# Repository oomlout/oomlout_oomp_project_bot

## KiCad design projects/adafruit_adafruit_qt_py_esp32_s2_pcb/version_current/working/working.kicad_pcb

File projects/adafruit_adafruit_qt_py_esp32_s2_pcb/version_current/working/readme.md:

# Adafruit-QT-Py-ESP32-S2-PCB by adafruit  
This is a harvested standardized copy of a project from github.  
The original project can be found at:  
https://github.com/adafruit/Adafruit-QT-Py-ESP32-S2-PCB  
Please consult that link for additional, details, files, and license information.  
Note: It was auto harvested and if the original repo had more than one board file or anything out of the ordinary the files here are likely not representative.

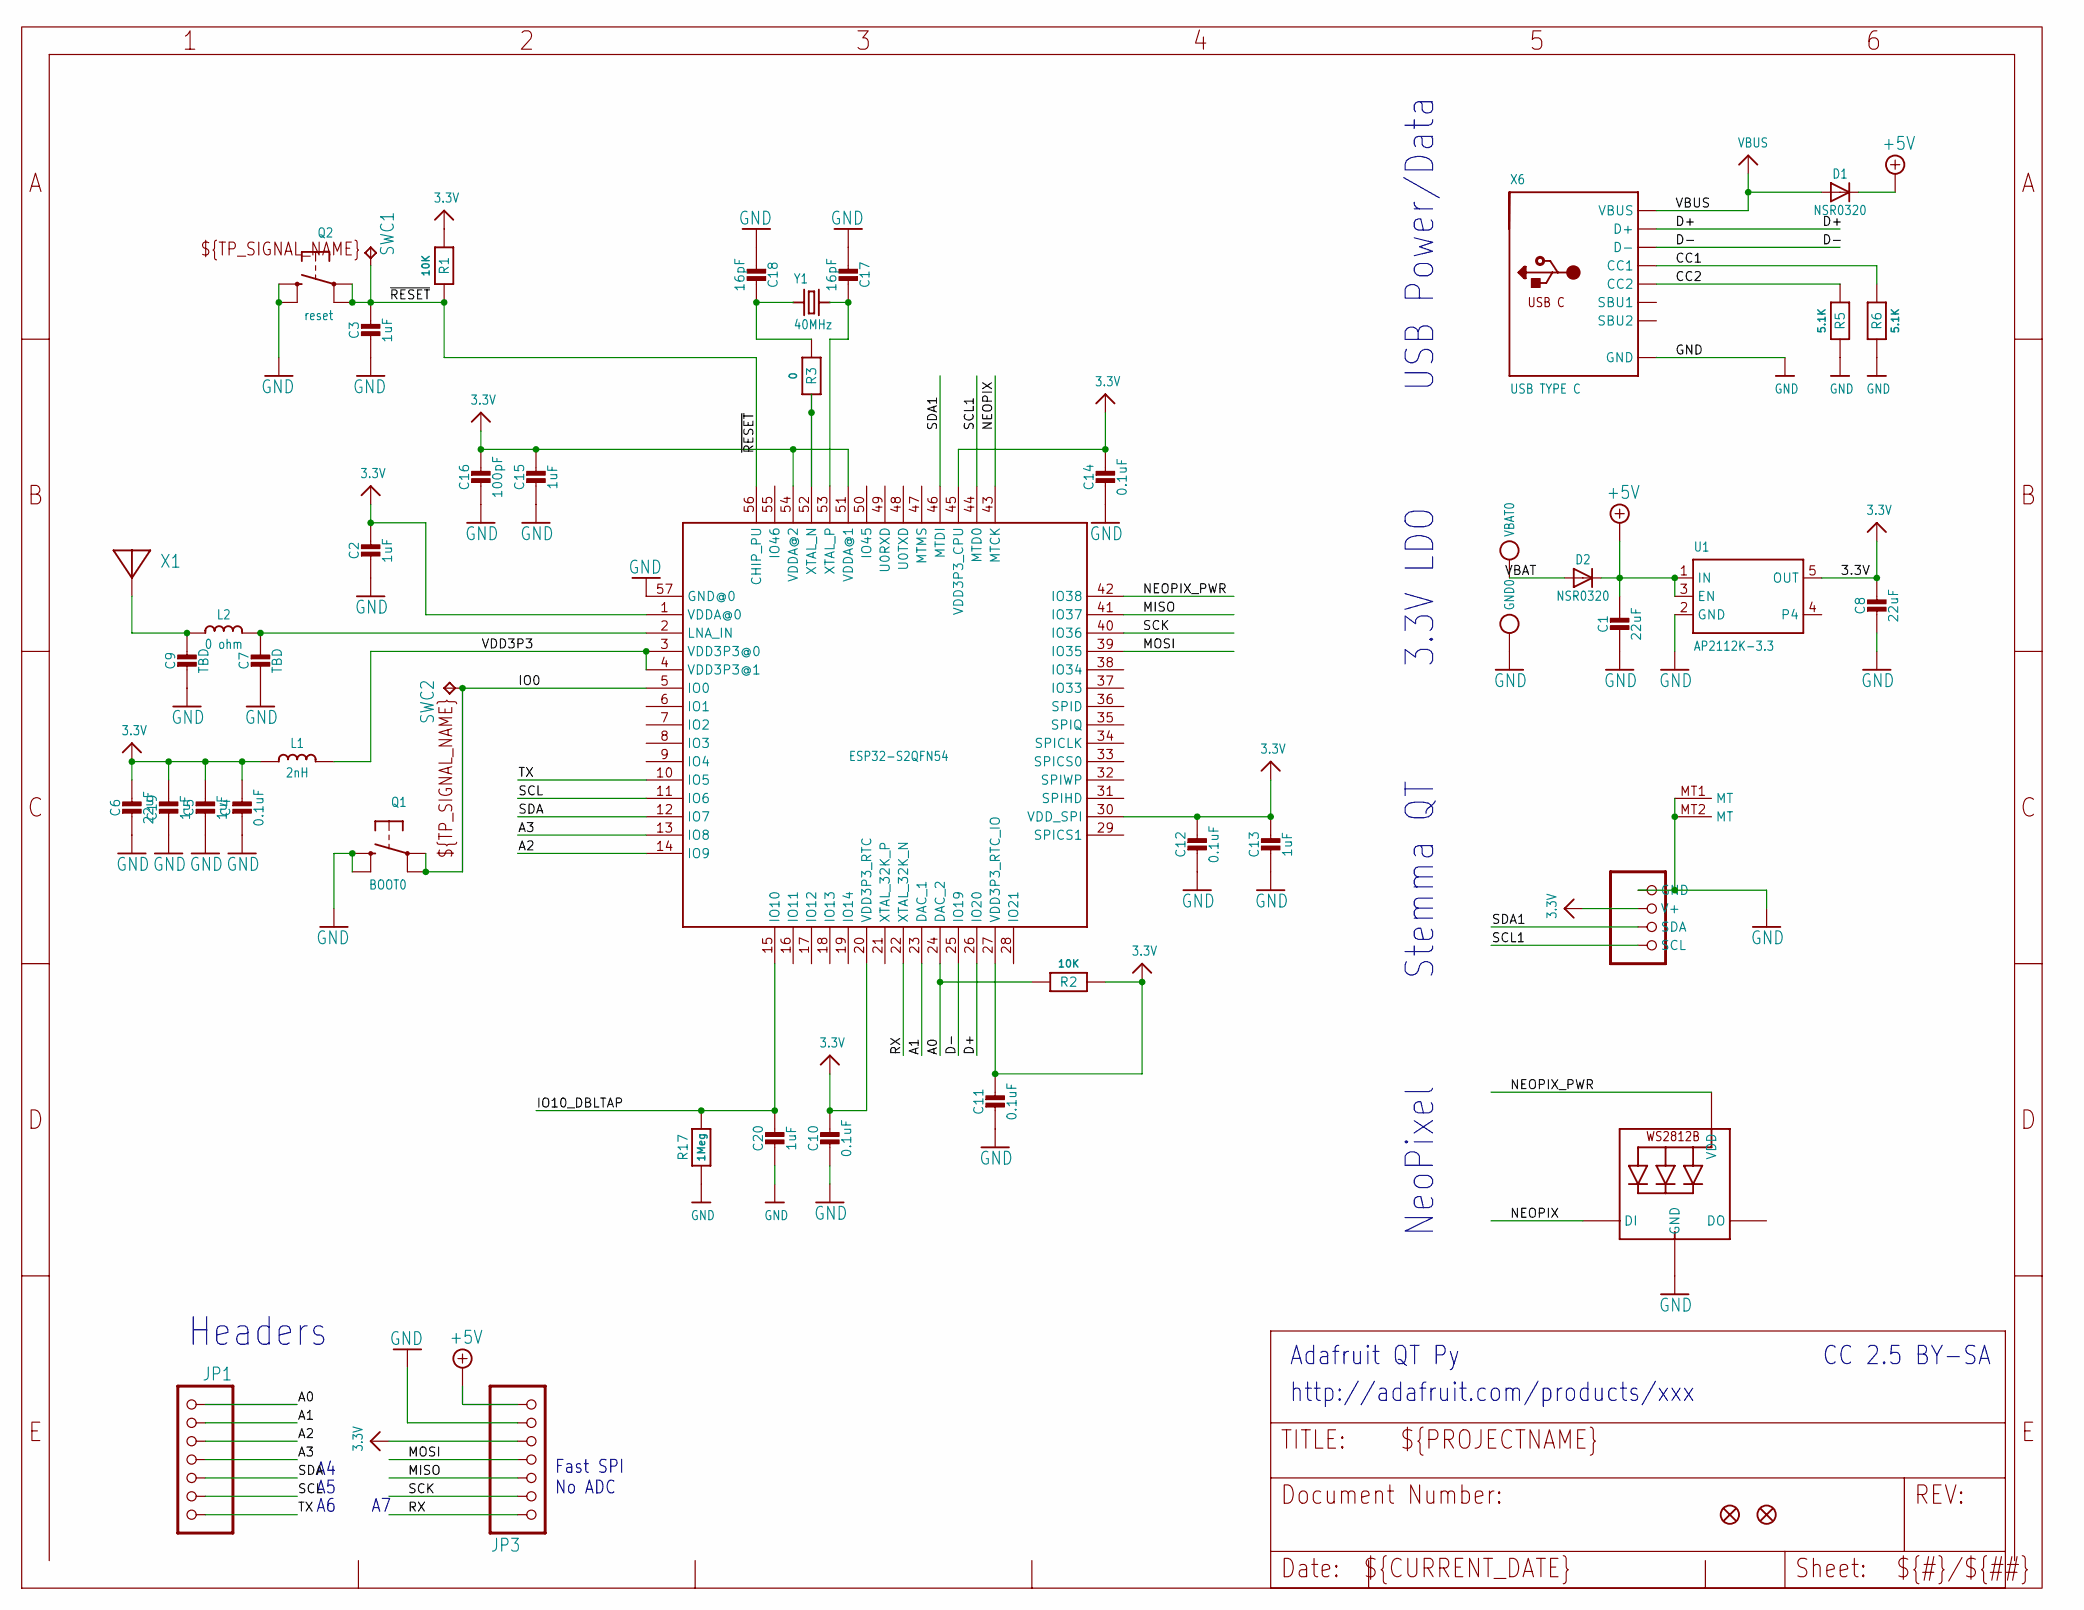
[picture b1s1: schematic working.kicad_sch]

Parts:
C1, C6, C8: 22uF; 0805-NO
C2, C3, C5, C13, C15, C19, C20: 1uF; _0402NO
C4, C10, C11, C12, C14: 0.1uF; _0402NO
C7, C9: TBD; _0402NO
C16: 100pF; _0402NO
C17, C18: 16pF; _0402NO
CONN1: STEMMA_I2C_QTSKINNY; JST_SH4_SKINNY
D1, D2: NSR0320; SOD-323_MINI
GND0: TESTPOINT_1X3; TESTPOINT_RECT_1X3MM
JP1, JP3: HEADER-1X7_CASTEL; 1X07_CASTEL
L1: 2nH; _0402
L2: 0 ohm; _0402
LED1: WS2812B_SK6805_1515; SK6805_1515
Q1: BOOT0; BTN_KMR2_4.6X2.8
Q2: reset; BTN_KMR2_4.6X2.8
R1, R2: 10K; _0402NO
R3: 0; _0402NO
R5, R6: 5.1K; _0402NO
R17: 1Meg; _0402NO
SWC1, SWC2: TPB1,27; B1,27
U1: AP2112K-3.3; SOT23-5
U$6, U$8: FIDUCIAL_1MM
U$15: ESP32-S2QFN54; QFN40P700X700X90-57T400N
VBAT0: TESTPOINT_1X3; TESTPOINT_RECT_1X3MM
X1: ANTENNA_JOHANSON_2450AT18B100; ANT_2450AT18B100
X6: USB TYPE C; USB_C_CUSB31-CFM2AX-01-X
Y1: 40MHz; CRYSTAL_2X1.6

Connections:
3.3V: C2.1, C4.1, C5.1, C6.1, C8.1, C10.1, C11.1, C12.1, C13.1, C14.1, C15.1, C16.1, C19.1, CONN1.2 (V+), JP3.5, JP3.5C (5), L1.1, R1.1, R2.1, U1.5 (OUT), U$15.1 (VDDA@0), U$15.20 (VDD3P3_RTC), U$15.27 (VDD3P3_RTC_IO), U$15.30 (VDD_SPI), U$15.45 (VDD3P3_CPU), U$15.51 (VDDA@1), U$15.54 (VDDA@2)
+5V: C1.1, D1.C, D2.C, JP3.7, JP3.7C (7), U1.1 (IN), U1.3 (EN)
A0: JP1.1, JP1.1C (1), R2.2, U$15.24 (DAC_2)
A1: JP1.2, JP1.2C (2), U$15.23 (DAC_1)
A2: JP1.3, JP1.3C (3), U$15.14 (IO9)
A3: JP1.4, JP1.4C (4), U$15.13 (IO8)
CC1: R6.2, X6.A5 (CC1)
CC2: R5.2, X6.B5 (CC2)
D+: U$15.26 (IO20), X6.A6 (D+), X6.B6 (D+)
D-: U$15.25 (IO19), X6.A7 (D-), X6.B7 (D-)
GND: C1.2, C2.2, C3.2, C4.2, C5.2, C6.2, C7.2, C8.2, C9.2, C10.2, C11.2, C12.2, C13.2, C14.2, C15.2, C16.2, C17.2, C18.2, C19.2, C20.2, CONN1.1 (GND), CONN1.MT1 (MT), CONN1.MT2 (MT), GND0.P$1, JP3.6, JP3.6C (6), LED1.4 (GND), Q1.B (S), Q1.B' (S1), Q2.B (S), Q2.B' (S1), R5.1, R6.1, R17.1, U1.2 (GND), U$15.57 (GND@0), X6.A1B12 (GND), X6.B1A12 (GND)
IO0: Q1.A, Q1.A' (P1), SWC2.TP, U$15.5 (IO0)
IO10_DBLTAP: C20.1, R17.2, U$15.15 (IO10)
MISO: JP3.3, JP3.3C (3), U$15.41 (IO37)
MOSI: JP3.4, JP3.4C (4), U$15.39 (IO35)
unnamed: C7.1, L2.2, U$15.2 (LNA_IN)
unnamed: C9.1, L2.1, X1.FP
unnamed: R3.2, U$15.52 (XTAL_N)
unnamed: C17.1, U$15.53 (XTAL_P), Y1.3 (2)
unnamed: C18.1, R3.1, Y1.1
NEOPIX: LED1.1 (DI), U$15.43 (MTCK)
NEOPIX_PWR: LED1.2 (VDD), U$15.42 (IO38)
RX: JP3.1, JP3.1C (1), U$15.22 (XTAL_32K_N)
SCK: JP3.2, JP3.2C (2), U$15.40 (IO36)
SCL: JP1.6, JP1.6C (6), U$15.11 (IO6)
SCL1: CONN1.4 (SCL), U$15.44 (MTD0)
SDA: JP1.5, JP1.5C (5), U$15.12 (IO7)
SDA1: CONN1.3 (SDA), U$15.46 (MTDI)
TX: JP1.7, JP1.7C (7), U$15.10 (IO5)
VBAT: D2.A, VBAT0.P$1
VBUS: D1.A, X6.A4B9 (VBUS), X6.B4A9 (VBUS)
VDD3P3: L1.2, U$15.3 (VDD3P3@0), U$15.4 (VDD3P3@1)
~RESET: C3.1, Q2.A, Q2.A' (P1), R1.2, SWC1.TP, U$15.56 (CHIP_PU)

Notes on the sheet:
USB Power/Data
CC 2.5 BY-SA
Adafruit QT Py
Headers
NeoPixel
http://adafruit.com/products/xxx
Fast SPI No ADC
Stemma QT
3.3V LDO

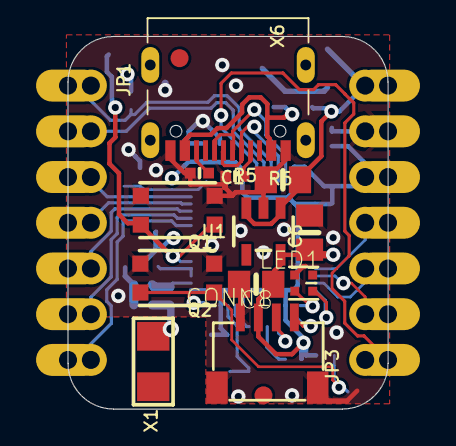
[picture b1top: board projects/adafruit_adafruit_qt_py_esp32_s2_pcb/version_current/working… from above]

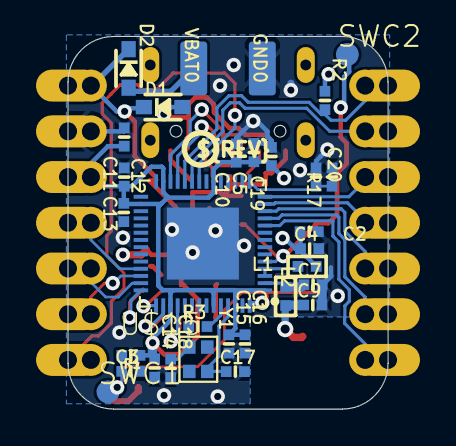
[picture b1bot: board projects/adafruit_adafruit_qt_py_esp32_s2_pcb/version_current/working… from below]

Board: 4 copper layers, 17.8 x 20.7 mm, 50 parts (33 on the bottom side), 33 nets.

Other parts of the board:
U$3: QTPYS2_TOP
U$7: QTPYS2_BOT
U$12: PCBFEAT-REV-040

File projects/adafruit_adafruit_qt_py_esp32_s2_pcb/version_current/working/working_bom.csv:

Row,Description,Part,References,Value,Footprint,Quantity Per PCB,Status,Datasheet
1,,CAP_CERAMIC_0402NO,C17 C18,16pF,_0402NO,2, ,
2,,CAP_CERAMIC_0402NO,C16,100pF,_0402NO,1, ,
3,,CAP_CERAMIC_0402NO,C4 C10 C11 C12 C14,0.1uF,_0402NO,5, ,
4,,CAP_CERAMIC_0402NO,C2 C3 C5 C13 C15 C19 C20,1uF,_0402NO,7, ,
5,,CAP_CERAMIC0805-NOOUTLINE,C1 C6 C8,22uF,0805-NO,3, ,
6,,CAP_CERAMIC_0402NO,C7 C9,TBD,_0402NO,2, ,
7,,STEMMA_I2C_QTSKINNY,CONN1,STEMMA_I2C_QTSKINNY,JST_SH4_SKINNY,1, ,
8,,DIODE_SOD323MINI,D1 D2,NSR0320,SOD-323_MINI,2, ,
9,,HEADER-1X7_CASTEL,JP1 JP3,HEADER-1X7_CASTEL,1X07_CASTEL,2, ,
10,,INDUCTOR_0402,L2,0 ohm,_0402,1, ,
11,,INDUCTOR_0402,L1,2nH,_0402,1, ,
12,,WS2812B_SK6805_1515,LED1,WS2812B_SK6805_1515,SK6805_1515,1, ,
13,,SWITCH_TACT_SMT4.6X2.8,Q1,BOOT0,BTN_KMR2_4.6X2.8,1, ,
14,,SWITCH_TACT_SMT4.6X2.8,Q2,reset,BTN_KMR2_4.6X2.8,1, ,
15,,RESISTOR_0402NO,R3,0,_0402NO,1, ,
16,,RESISTOR_0402NO,R5 R6,5.1K,_0402NO,2, ,
17,,RESISTOR_0402NO,R1 R2,10K,_0402NO,2, ,
18,,RESISTOR_0402NO,R17,1Meg,_0402NO,1, ,
19,,"TPB1,27",SWC1 SWC2,"TPB1,27","B1,27",2, ,
20,,VREG_SOT23-5,U1,AP2112K-3.3,SOT23-5,1, ,
21,,ESP32-S2QFN54,U$15,ESP32-S2QFN54,QFN40P700X700X90-57T400N,1, ,
22,,ANTENNA_JOHANSON_2450AT18B100,X1,ANTENNA_JOHANSON_2450AT18B100,ANT_2450AT18B100,1, ,
23,,USB_C,X6,USB TYPE C,USB_C_CUSB31-CFM2AX-01-X,1, ,
24,,CRYSTAL_2X1.6MM,Y1,40MHz,CRYSTAL_2X1.6,1, ,





Project info:
Schematic:,working
Variant:,default
Revision:,
Date:,2023-08-03_17-21-23
KiCad Version:,7.0.6-7.0.6~ubuntu22.04.1
Statistics:
Component Groups:,24
Component Count:,43 (0 SMD/ 0 THT)
Fitted Components:,43 (0 SMD/ 0 THT)
Number of PCBs:,1
Total Components:,43

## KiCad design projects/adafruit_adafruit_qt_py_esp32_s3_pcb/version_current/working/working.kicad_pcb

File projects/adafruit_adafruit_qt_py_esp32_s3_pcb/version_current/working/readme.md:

# OOMP Project  
## Adafruit-QT-Py-ESP32-S3-PCB  by adafruit  
  
oomp key: oomp_projects_flat_adafruit_adafruit_qt_py_esp32_s3_pcb  
(snippet of original readme)  
  
-- Adafruit QT Py ESP32-S3 WiFi Dev Board PCB  
  
<a href="http://www.adafruit.com/products/5426"><br/>  
Click here to purchase one from the Adafruit shop</a>  
  
PCB files for the Adafruit QT Py ESP32-S3 WiFi Dev Board.   
  
Format is EagleCAD schematic and board layout  
* https://www.adafruit.com/product/5426  
  
--- Description  
  
The ESP32-S3 has arrived in QT Py format - and what a great way to get started with this powerful new chip from Espressif! With dual 240 MHz cores, WiFi and BLE support, and native USB, this QT Py is great for powering your IoT projects.  
  
The ESP32-S3 is a highly-integrated, low-power, 2.4 GHz Wi-Fi System-on-Chip (SoC) solution that now has WiFi and BLE support, built-in native USB as well as some other interesting new technologies like Time of Flight distance measurements. With its state-of-the-art power and RF performance, this SoC is an ideal choice for a wide variety of application scenarios relating to the Internet of Things (IoT), wearable electronics, and smart homes.   
  
With native USB and 8 MB Flash this board will let you upgrade your existing ESP32 projects. Native USB means it can act like a keyboard or a disk drive, and no external USB-to-Serial converter required. WiFi and BLE mean it's awesome for IoT projects.  
  
OLEDs! Inertial Measurement Units! Sensors a-plenty. All plug-and-play thanks to the innovative chainable design: SparkFun Qwiic-compatible STEMMA QT connectors for the I2C bus so you don't  
  full source readme at [readme_src.md](readme_src.md)  
  
source repo at: [https://github.com/adafruit/Adafruit-QT-Py-ESP32-S3-PCB](https://github.com/adafruit/Adafruit-QT-Py-ESP32-S3-PCB)  
## Board  

## Schematic  

[schematic pdf](working_schematic.pdf)  
## Images

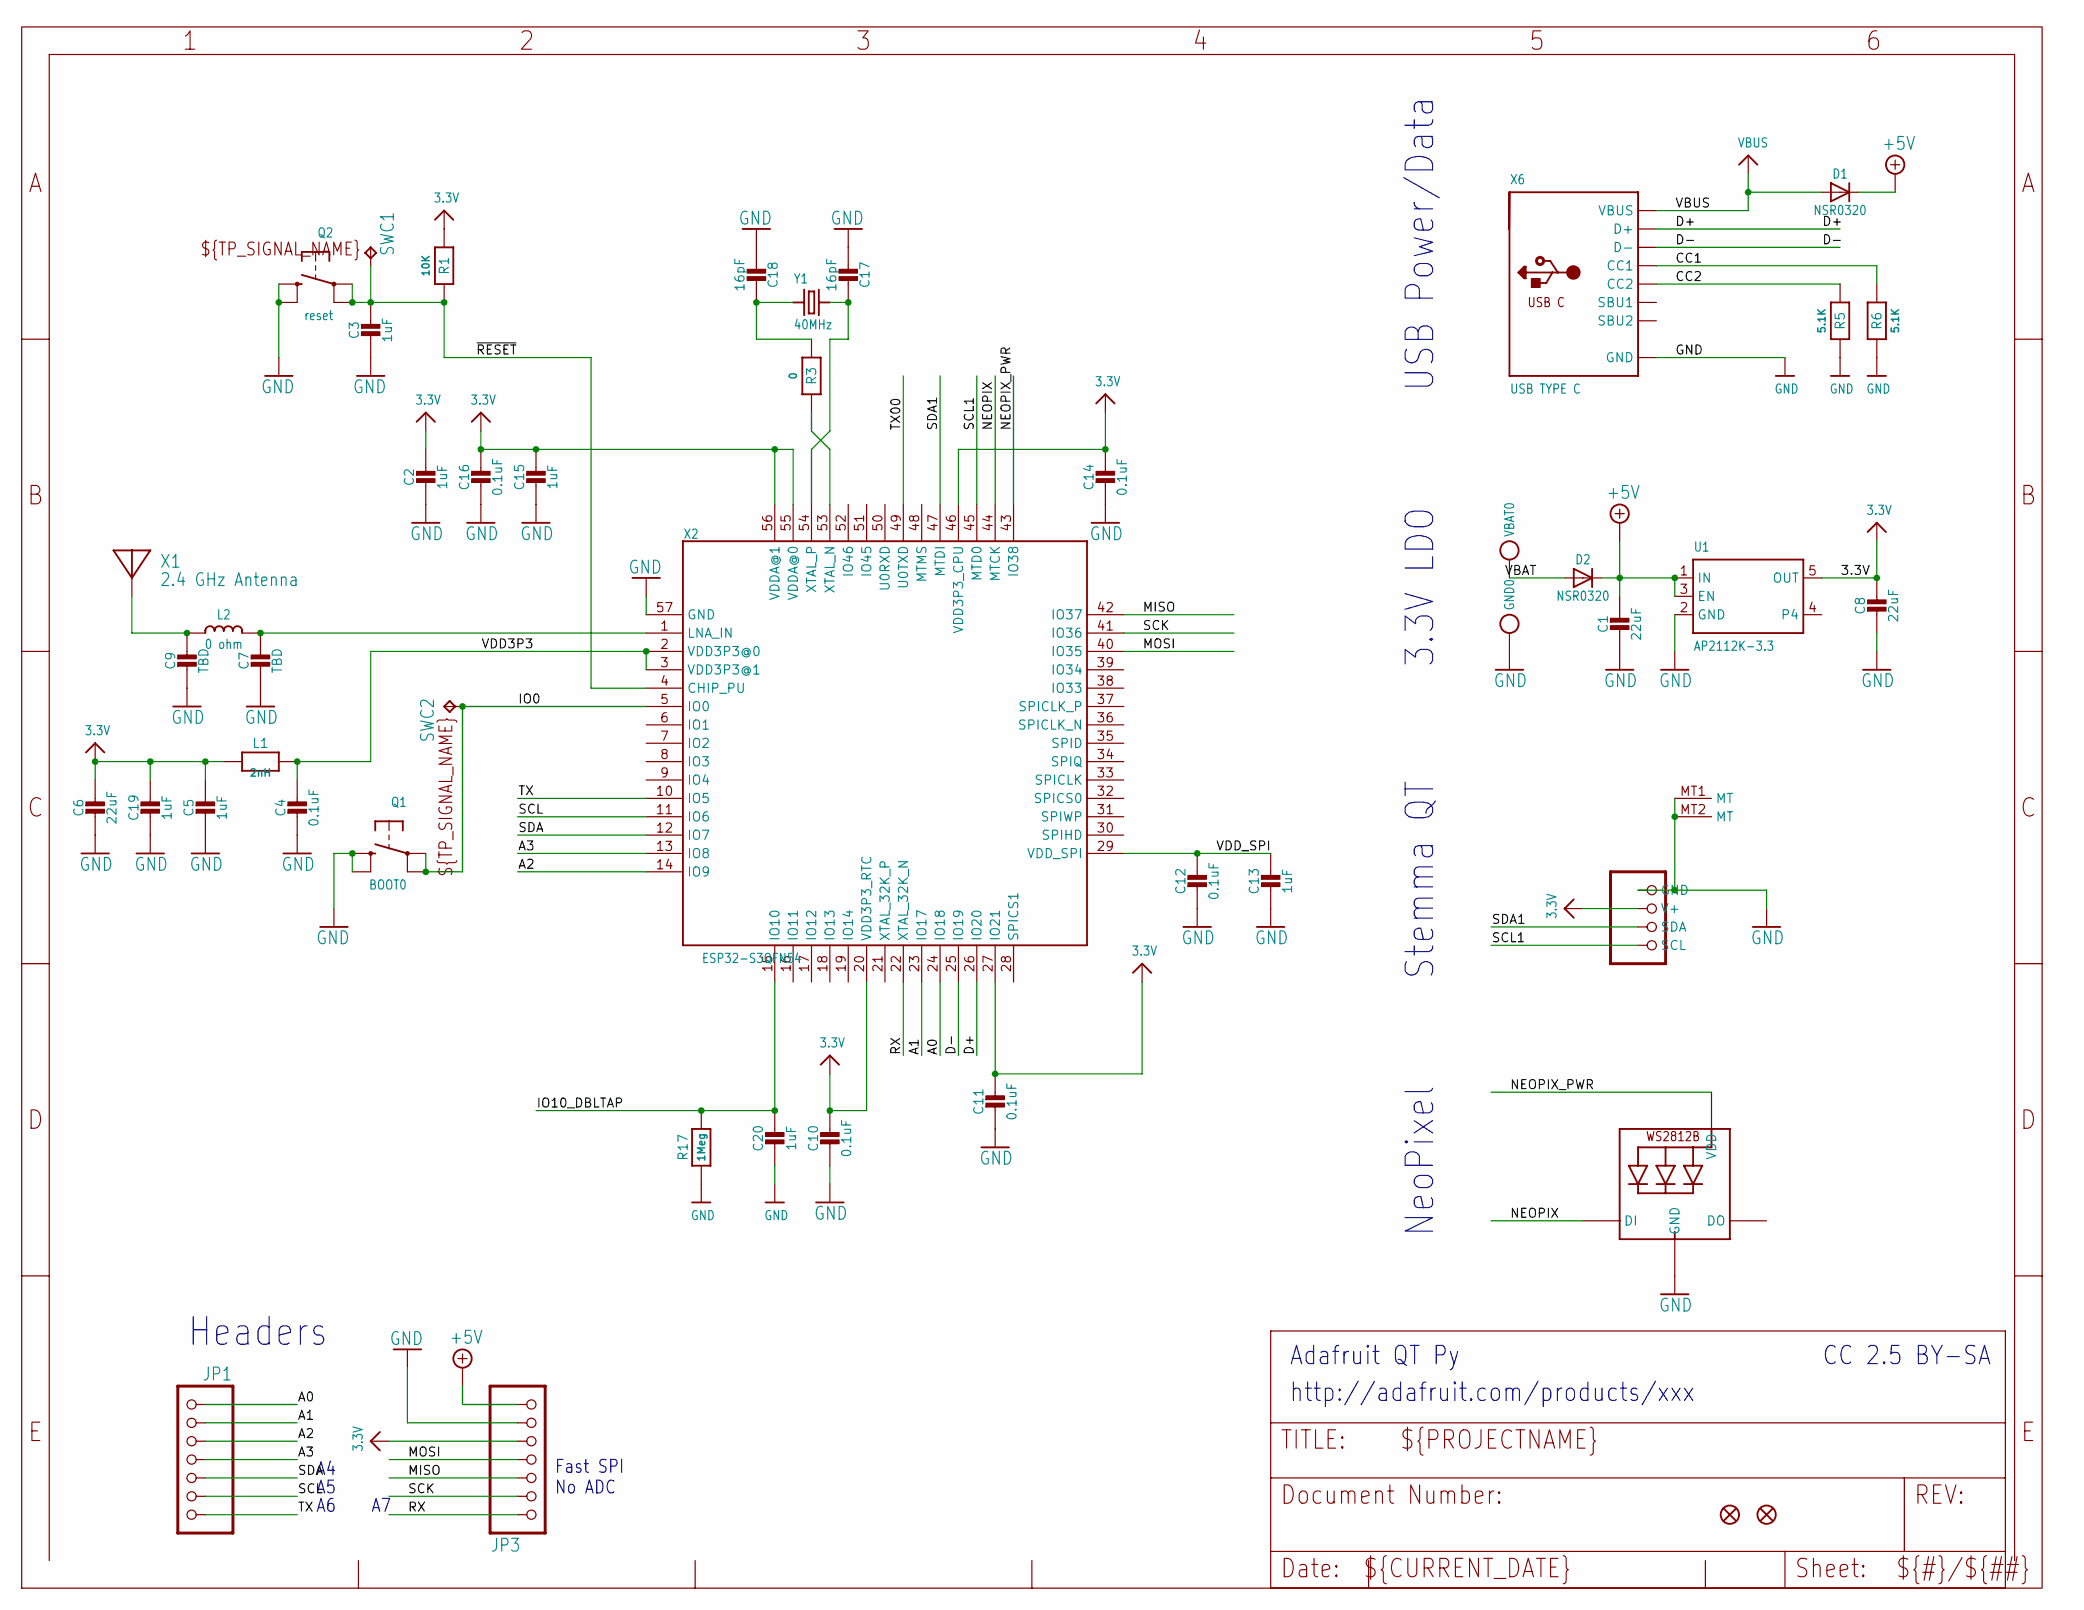
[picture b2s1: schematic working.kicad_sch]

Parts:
C1, C6, C8: 22uF; 0805-NO
C2, C3, C5, C13, C15, C19, C20: 1uF; _0402NO
C4, C10, C11, C12, C14, C16: 0.1uF; _0402NO
C7, C9: TBD; _0402NO
C17, C18: 16pF; _0402NO
CONN1: STEMMA_I2C_QTSKINNY; JST_SH4_SKINNY
D1, D2: NSR0320; SOD-323_MINI
GND0: TESTPOINT_MINUS; TESTPOINT_MINUS_1X3MM
JP1, JP3: HEADER-1X7_CASTEL; 1X07_CASTEL
L1: 2nH; _0402NO
L2: 0 ohm; _0402
LED1: WS2812B_SK6805_1515; SK6805_1515
Q1: BOOT0; BTN_KMR2_4.6X2.8
Q2: reset; BTN_KMR2_4.6X2.8
R1: 10K; _0402NO
R3: 0; _0402NO
R5, R6: 5.1K; _0402NO
R17: 1Meg; _0402NO
SWC1, SWC2: TPB1,27; B1,27
U1: AP2112K-3.3; SOT23-5
U$6, U$8: FIDUCIAL_1MM
VBAT0: TESTPOINT_PLUS13; TESTPOINT_PLUS_1X3MM
X1: 2.4 GHz Antenna; ANT_2450AT18B100
X2: ESP32-S3QFN54; QFN56_7X7
X6: USB TYPE C; USB_C_CUSB31-CFM2AX-01-X
Y1: 40MHz; CRYSTAL_2X1.6

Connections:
3.3V: C2.1, C5.1, C6.1, C8.1, C10.1, C11.1, C14.1, C15.1, C16.1, C19.1, CONN1.2 (V+), JP3.5, JP3.5C (5), L1.1, R1.1, U1.5 (OUT), X2.20 (VDD3P3_RTC), X2.27 (IO21), X2.46 (VDD3P3_CPU), X2.55 (VDDA@0), X2.56 (VDDA@1)
+5V: C1.1, D1.C, D2.C, JP3.7, JP3.7C (7), U1.1 (IN), U1.3 (EN)
A0: JP1.1, JP1.1C (1), X2.24 (IO18)
A1: JP1.2, JP1.2C (2), X2.23 (IO17)
A2: JP1.3, JP1.3C (3), X2.14 (IO9)
A3: JP1.4, JP1.4C (4), X2.13 (IO8)
CC1: R6.2, X6.A5 (CC1)
CC2: R5.2, X6.B5 (CC2)
D+: X2.26 (IO20), X6.A6 (D+), X6.B6 (D+)
D-: X2.25 (IO19), X6.A7 (D-), X6.B7 (D-)
GND: C1.2, C2.2, C3.2, C4.2, C5.2, C6.2, C7.2, C8.2, C9.2, C10.2, C11.2, C12.2, C13.2, C14.2, C15.2, C16.2, C17.2, C18.2, C19.2, C20.2, CONN1.1 (GND), CONN1.MT1 (MT), CONN1.MT2 (MT), GND0.P$1, JP3.6, JP3.6C (6), LED1.4 (GND), Q1.B (S), Q1.B' (S1), Q2.B (S), Q2.B' (S1), R5.1, R6.1, R17.1, U1.2 (GND), X2.57 (GND), X6.A1B12 (GND), X6.B1A12 (GND)
IO0: Q1.A, Q1.A' (P1), SWC2.TP, X2.5 (IO0)
IO10_DBLTAP: C20.1, R17.2, X2.15 (IO10)
MISO: JP3.3, JP3.3C (3), X2.42 (IO37)
MOSI: JP3.4, JP3.4C (4), X2.40 (IO35)
unnamed: R3.2, X2.53 (XTAL_N)
unnamed: C7.1, L2.2, X2.1 (LNA_IN)
unnamed: C9.1, L2.1, X1.FP
unnamed: C17.1, X2.54 (XTAL_P), Y1.3 (2)
unnamed: C18.1, R3.1, Y1.1
NEOPIX: LED1.1 (DI), X2.44 (MTCK)
NEOPIX_PWR: LED1.2 (VDD), X2.43 (IO38)
RX: JP3.1, JP3.1C (1), X2.22 (XTAL_32K_N)
SCK: JP3.2, JP3.2C (2), X2.41 (IO36)
SCL: JP1.6, JP1.6C (6), X2.11 (IO6)
SCL1: CONN1.4 (SCL), X2.45 (MTD0)
SDA: JP1.5, JP1.5C (5), X2.12 (IO7)
SDA1: CONN1.3 (SDA), X2.47 (MTDI)
TX: JP1.7, JP1.7C (7), X2.10 (IO5)
TX00: X2.49 (U0TXD)
VBAT: D2.A, VBAT0.P$1
VBUS: D1.A, X6.A4B9 (VBUS), X6.B4A9 (VBUS)
VDD3P3: C4.1, L1.2, X2.2 (VDD3P3@0), X2.3 (VDD3P3@1)
VDD_SPI: C12.1, C13.1, X2.29 (VDD_SPI)
~RESET: C3.1, Q2.A, Q2.A' (P1), R1.2, SWC1.TP, X2.4 (CHIP_PU)

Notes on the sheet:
Stemma QT
http://adafruit.com/products/xxx
USB Power/Data
NeoPixel
Adafruit QT Py
Fast SPI No ADC
CC 2.5 BY-SA
Headers
3.3V LDO

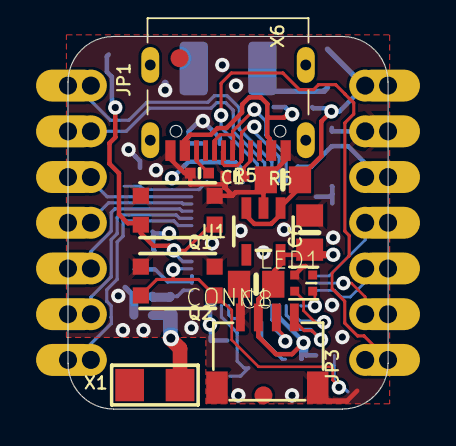
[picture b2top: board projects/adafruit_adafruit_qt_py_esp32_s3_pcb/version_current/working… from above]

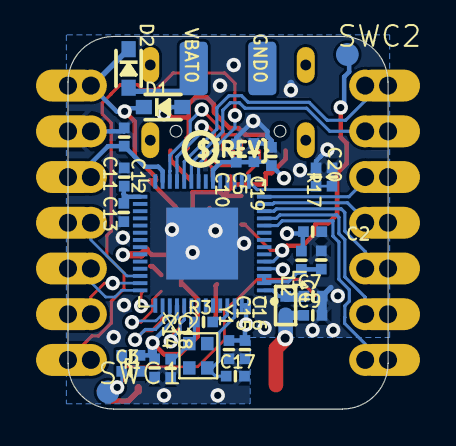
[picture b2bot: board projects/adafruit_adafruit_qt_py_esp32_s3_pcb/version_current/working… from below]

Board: 4 copper layers, 17.8 x 20.7 mm, 49 parts (32 on the bottom side), 34 nets.

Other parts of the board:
U$7: QTPY_ESP32_TOP
U$11: QTPYS3_BOT
U$12: PCBFEAT-REV-040

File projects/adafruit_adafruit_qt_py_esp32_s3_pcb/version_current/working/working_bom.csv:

Row,Description,Part,References,Value,Footprint,Quantity Per PCB,Status,Datasheet
1,,CAP_CERAMIC_0402NO,C17 C18,16pF,_0402NO,2, ,
2,,CAP_CERAMIC_0402NO,C4 C10 C11 C12 C14 C16,0.1uF,_0402NO,6, ,
3,,CAP_CERAMIC_0402NO,C2 C3 C5 C13 C15 C19 C20,1uF,_0402NO,7, ,
4,,CAP_CERAMIC0805-NOOUTLINE,C1 C6 C8,22uF,0805-NO,3, ,
5,,CAP_CERAMIC_0402NO,C7 C9,TBD,_0402NO,2, ,
6,,STEMMA_I2C_QTSKINNY,CONN1,STEMMA_I2C_QTSKINNY,JST_SH4_SKINNY,1, ,
7,,DIODE_SOD323MINI,D1 D2,NSR0320,SOD-323_MINI,2, ,
8,,HEADER-1X7_CASTEL,JP1 JP3,HEADER-1X7_CASTEL,1X07_CASTEL,2, ,
9,,INDUCTOR_0402,L2,0 ohm,_0402,1, ,
10,,RESISTOR_0402NO,L1,2nH,_0402NO,1, ,
11,,WS2812B_SK6805_1515,LED1,WS2812B_SK6805_1515,SK6805_1515,1, ,
12,,SWITCH_TACT_SMT4.6X2.8,Q1,BOOT0,BTN_KMR2_4.6X2.8,1, ,
13,,SWITCH_TACT_SMT4.6X2.8,Q2,reset,BTN_KMR2_4.6X2.8,1, ,
14,,RESISTOR_0402NO,R3,0,_0402NO,1, ,
15,,RESISTOR_0402NO,R5 R6,5.1K,_0402NO,2, ,
16,,RESISTOR_0402NO,R1,10K,_0402NO,1, ,
17,,RESISTOR_0402NO,R17,1Meg,_0402NO,1, ,
18,,"TPB1,27",SWC1 SWC2,"TPB1,27","B1,27",2, ,
19,,VREG_SOT23-5,U1,AP2112K-3.3,SOT23-5,1, ,
20,,ANTENNA_JOHANSON_2450AT18B100,X1,2.4 GHz Antenna,ANT_2450AT18B100,1, ,
21,,ESP32-S3QFN54,X2,ESP32-S3QFN54,QFN56_7X7,1, ,
22,,USB_C,X6,USB TYPE C,USB_C_CUSB31-CFM2AX-01-X,1, ,
23,,CRYSTAL_2X1.6MM,Y1,40MHz,CRYSTAL_2X1.6,1, ,





Project info:
Schematic:,working
Variant:,default
Revision:,
Date:,2023-08-03_17-21-23
KiCad Version:,7.0.6-7.0.6~ubuntu22.04.1
Statistics:
Component Groups:,23
Component Count:,42 (0 SMD/ 0 THT)
Fitted Components:,42 (0 SMD/ 0 THT)
Number of PCBs:,1
Total Components:,42

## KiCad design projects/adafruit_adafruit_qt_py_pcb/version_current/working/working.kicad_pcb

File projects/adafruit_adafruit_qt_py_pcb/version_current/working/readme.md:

# OOMP Project  
## Adafruit-QT-Py-PCB  by adafruit  
  
oomp key: oomp_projects_flat_adafruit_adafruit_qt_py_pcb  
(snippet of original readme)  
  
-- Adafruit QT Py PCB  
  
<a href="http://www.adafruit.com/products/4600"><br/>  
Click here to purchase one from the Adafruit shop</a>  
  
PCB files for the Adafruit QT Py.  
  
Format is EagleCAD schematic and board layout  
* https://www.adafruit.com/product/4600  
  
--- Description  
  
What a cutie pie! Or is it... a QT Py? This diminutive dev board comes with our favorite lil chip, the SAMD21 (as made famous in our GEMMA M0 and Trinket M0 boards).  
  
This time it comes with our favorite connector - the STEMMA QT, a chainable I2C port that can be used with any of our STEMMA QT sensors and accessories.  
  
OLEDs! Inertial Measurment Units! Sensors a-plenty. All plug-and-play thanks to the innovative chainable design: SparkFun Qwiic-compatible STEMMA QT connectors for the I2C bus so you don't even need to solder! Just plug in a compatible cable and attach it to your MCU of choice, and you’re ready to load up some software and measure some light.  
  
Use any SparkFun Qwiic boards! Seeed Grove I2C boards will also work with this adapter cable.  
  
Pinout and shape is Seeed Xiao compatible, with castellated pads so you can solder it flat to a PCB. In addition to the QT connector, we also added an RGB NeoPixel (with controllable power pin to allow for ultra-low-power usage), and a reset button (great for restarting your program, or entering the bootloader)  
  
Runs Arduino like a dream, and can be used for basic CircuitPython projects. For more advanced usage li  
  full source readme at [readme_src.md](readme_src.md)  
  
source repo at: [https://github.com/adafruit/Adafruit-QT-Py-PCB](https://github.com/adafruit/Adafruit-QT-Py-PCB)  
## Board  

## Schematic  

[schematic pdf](working_schematic.pdf)  
## Images

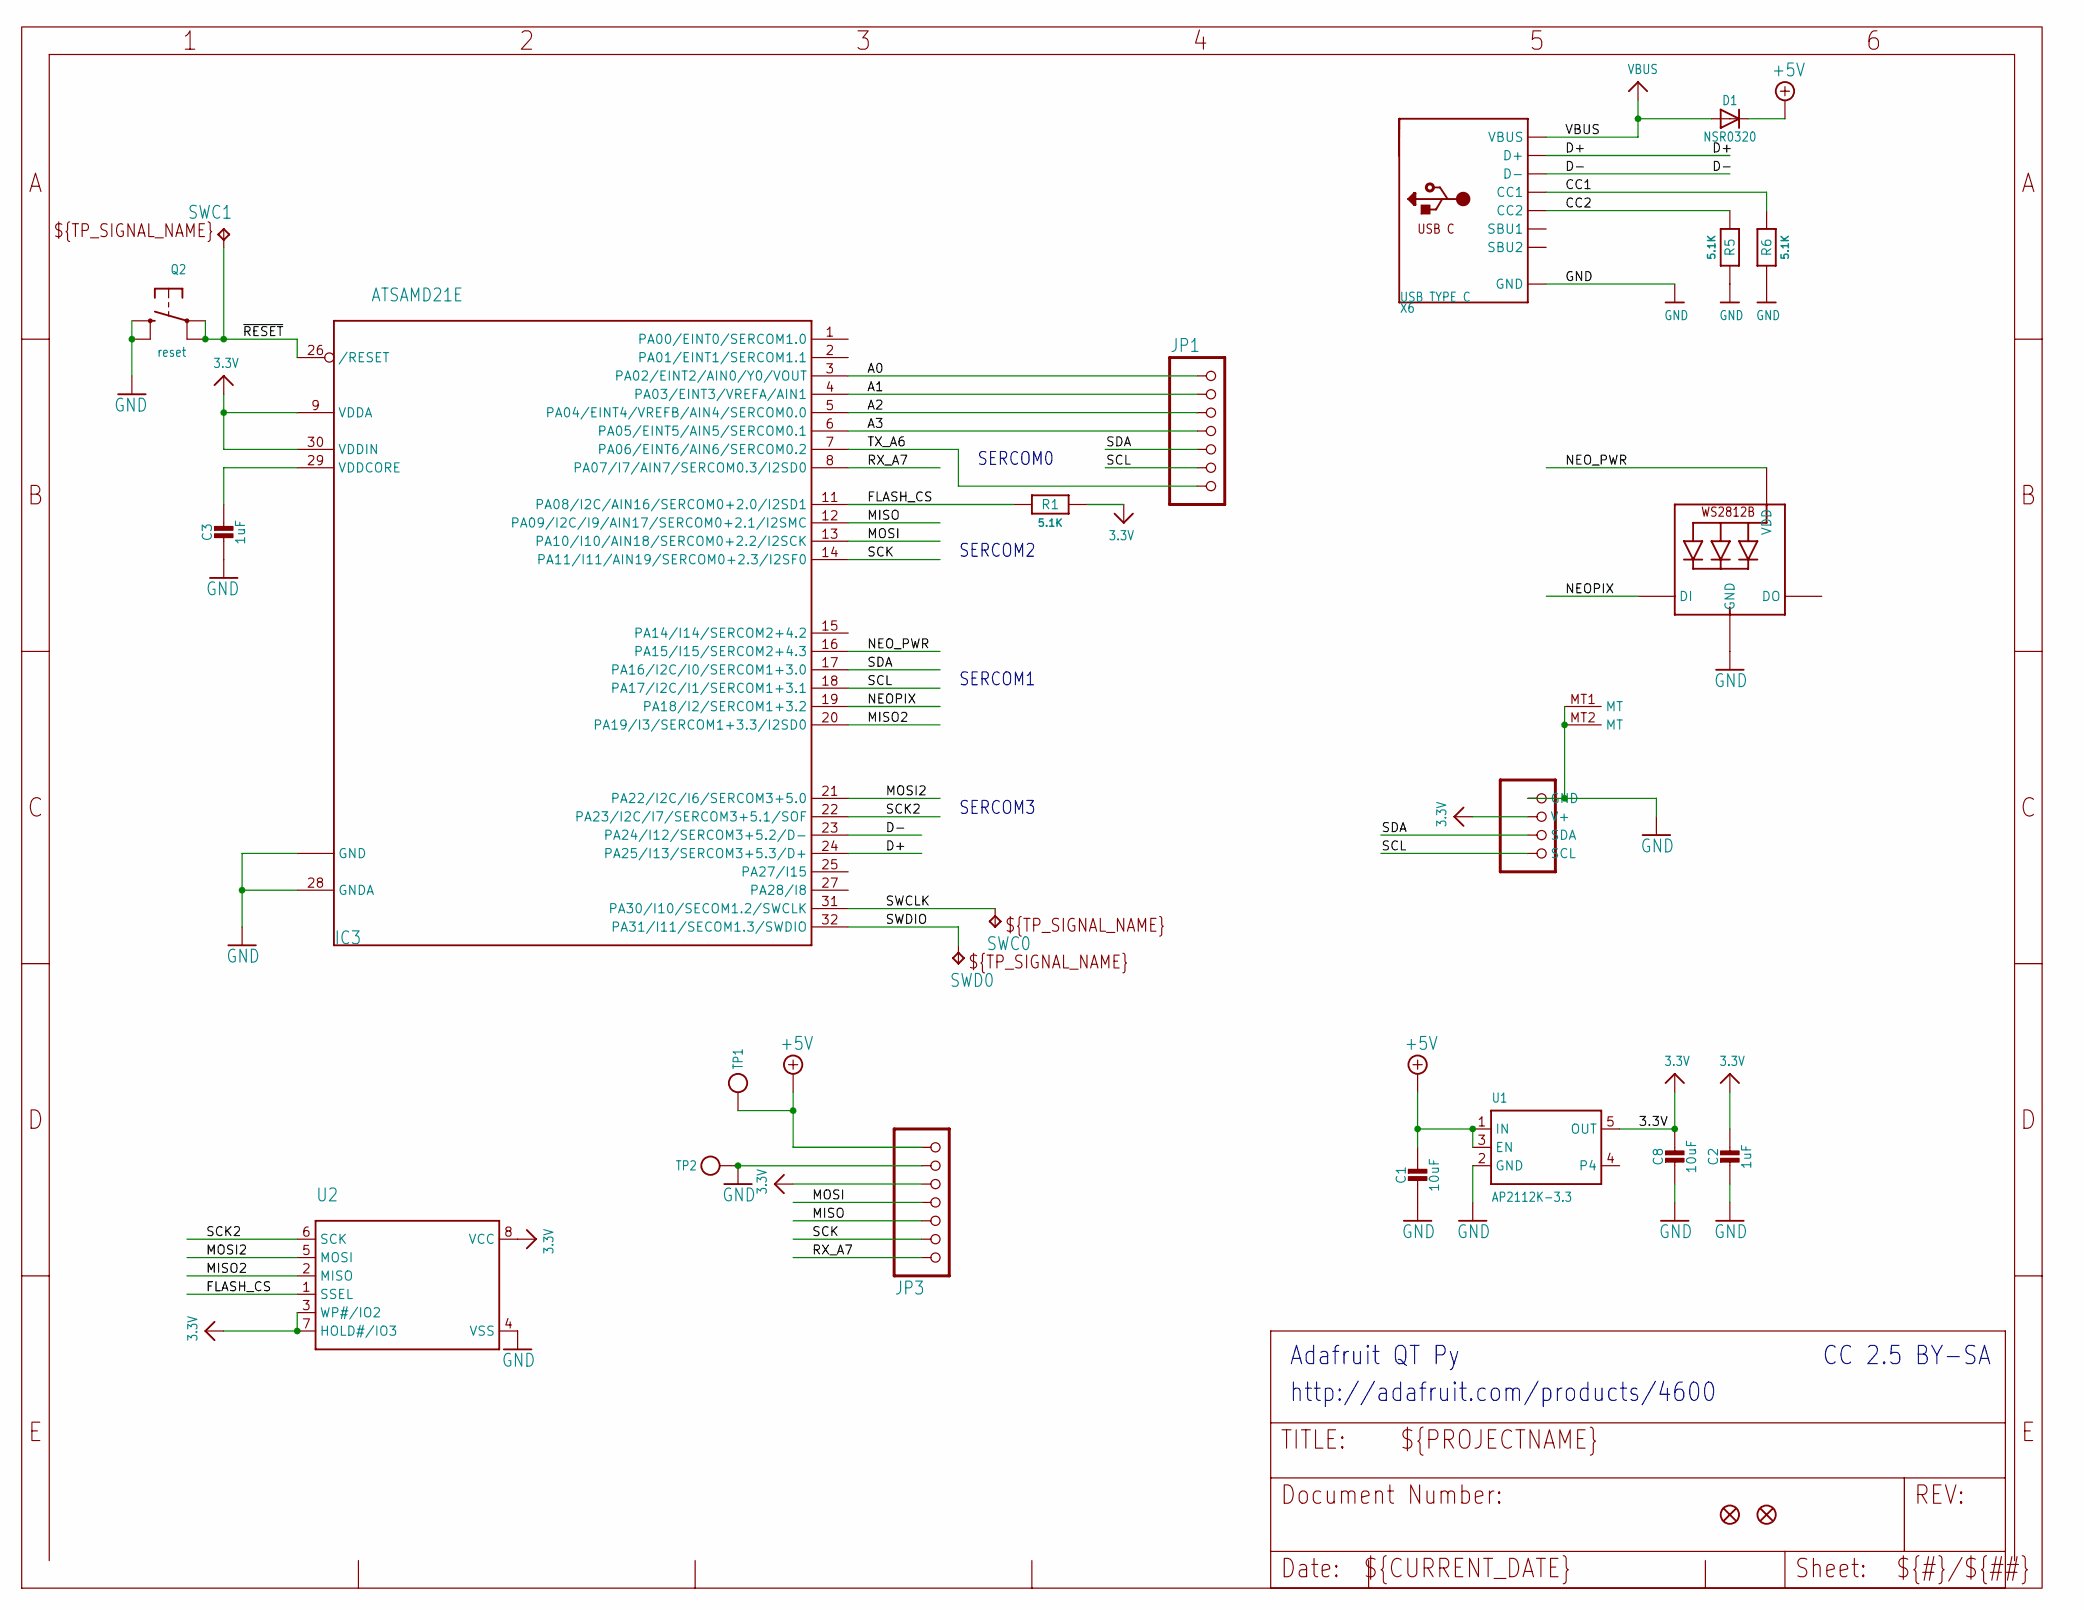
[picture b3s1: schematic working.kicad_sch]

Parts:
C1, C8: 10uF; _0805MP
C2, C3: 1uF; _0402NO
CONN1: STEMMA_I2C_QTSKINNY; JST_SH4_SKINNY
D1: NSR0320; SOD-323_MINI
IC3: ATSAMD21E; QFN32_5MM
JP1, JP3: HEADER-1X7_CASTEL; 1X07_CASTEL
LED1: WS2812B_SK6805_1515; SK6805_1515
Q2: reset; BTN_KMR2_4.6X2.8
R1, R5, R6: 5.1K; _0402NO
SWC0, SWC1: TPB1,27; B1,27
SWD0: TPB1,27; B1,27
TP1, TP2: TESTPOINT_1X3; TESTPOINT_RECT_1X3MM
U1: AP2112K-3.3; SOT23-5
U2: SPIFLASH_8PIN; SOIC8_150MIL
U$6, U$8: FIDUCIAL_1MM
X6: USB TYPE C; USB_C_CUSB31-CFM2AX-01-X

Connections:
3.3V: C2.1, C8.1, CONN1.2 (V+), IC3.9 (VDDA), IC3.30 (VDDIN), JP3.5, JP3.5C (5), R1.1, U1.5 (OUT), U2.3 (WP#/IO2), U2.7 (HOLD#/IO3), U2.8 (VCC)
+5V: C1.1, D1.C, JP3.7, JP3.7C (7), TP1.P$1, U1.1 (IN), U1.3 (EN)
A0: IC3.3 (PA02/EINT2/AIN0/Y0/VOUT), JP1.1, JP1.1C (1)
A1: IC3.4 (PA03/EINT3/VREFA/AIN1), JP1.2, JP1.2C (2)
A2: IC3.5 (PA04/EINT4/VREFB/AIN4/SERCOM0.0), JP1.3, JP1.3C (3)
A3: IC3.6 (PA05/EINT5/AIN5/SERCOM0.1), JP1.4, JP1.4C (4)
CC1: R6.2, X6.A5 (CC1)
CC2: R5.2, X6.B5 (CC2)
D+: IC3.24 (PA25/I13/SERCOM3+5.3/D+), X6.A6 (D+), X6.B6 (D+)
D-: IC3.23 (PA24/I12/SERCOM3+5.2/D-), X6.A7 (D-), X6.B7 (D-)
FLASH_CS: IC3.11 (PA08/I2C/AIN16/SERCOM0+2.0/I2SD1), R1.2, U2.1 (SSEL)
GND: C1.2, C2.2, C3.2, C8.2, CONN1.1 (GND), CONN1.MT1 (MT), CONN1.MT2 (MT), IC3.10 (GND), IC3.28 (GNDA), IC3.33 (GND), JP3.6, JP3.6C (6), LED1.4 (GND), Q2.B (S), Q2.B' (S1), R5.1, R6.1, TP2.P$1, U1.2 (GND), U2.4 (VSS), X6.A1B12 (GND), X6.B1A12 (GND)
MISO: IC3.12 (PA09/I2C/I9/AIN17/SERCOM0+2.1/I2SMC), JP3.3, JP3.3C (3)
MISO2: IC3.20 (PA19/I3/SERCOM1+3.3/I2SD0), U2.2 (MISO)
MOSI: IC3.13 (PA10/I10/AIN18/SERCOM0+2.2/I2SCK), JP3.4, JP3.4C (4)
MOSI2: IC3.21 (PA22/I2C/I6/SERCOM3+5.0), U2.5 (MOSI)
NEOPIX: IC3.19 (PA18/I2/SERCOM1+3.2), LED1.1 (DI)
NEO_PWR: IC3.16 (PA15/I15/SERCOM2+4.3), LED1.2 (VDD)
RX_A7: IC3.8 (PA07/I7/AIN7/SERCOM0.3/I2SD0), JP3.1, JP3.1C (1)
SCK: IC3.14 (PA11/I11/AIN19/SERCOM0+2.3/I2SF0), JP3.2, JP3.2C (2)
SCK2: IC3.22 (PA23/I2C/I7/SERCOM3+5.1/SOF), U2.6 (SCK)
SCL: CONN1.4 (SCL), IC3.18 (PA17/I2C/I1/SERCOM1+3.1), JP1.6, JP1.6C (6)
SDA: CONN1.3 (SDA), IC3.17 (PA16/I2C/I0/SERCOM1+3.0), JP1.5, JP1.5C (5)
SWCLK: IC3.31 (PA30/I10/SECOM1.2/SWCLK), SWC0.TP
SWDIO: IC3.32 (PA31/I11/SECOM1.3/SWDIO), SWD0.TP
TX_A6: IC3.7 (PA06/EINT6/AIN6/SERCOM0.2), JP1.7, JP1.7C (7)
VBUS: D1.A, X6.A4B9 (VBUS), X6.B4A9 (VBUS)
VDDCORE: C3.1, IC3.29 (VDDCORE)
~RESET: IC3.26 (/RESET), Q2.A, Q2.A' (P1), SWC1.TP

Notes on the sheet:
SERCOM0
SERCOM1
CC 2.5 BY-SA
http://adafruit.com/products/4600
SERCOM2
SERCOM3
Adafruit QT Py

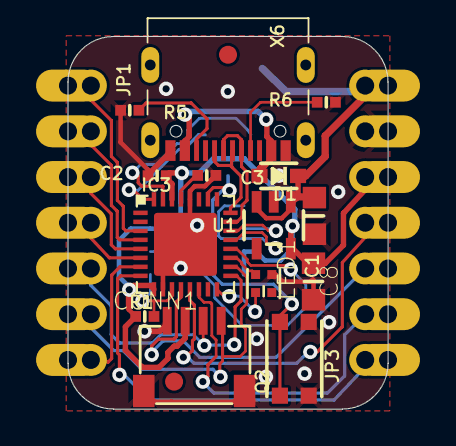
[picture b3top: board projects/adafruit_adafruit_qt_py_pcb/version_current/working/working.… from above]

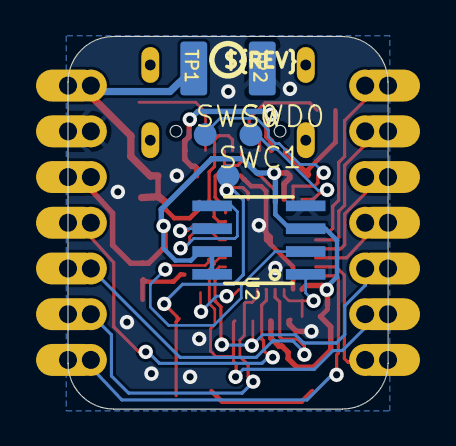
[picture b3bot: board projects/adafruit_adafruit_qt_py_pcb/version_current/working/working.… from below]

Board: 16 copper layers, 17.8 x 20.7 mm, 27 parts (8 on the bottom side), 29 nets.

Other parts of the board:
U$11: QTPY_BOT
U$12: PCBFEAT-REV-040
U$13: QTPY_TOP

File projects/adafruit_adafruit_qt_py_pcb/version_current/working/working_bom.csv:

Row,Description,Part,References,Value,Footprint,Quantity Per PCB,Status,Datasheet
1,,CAP_CERAMIC_0402NO,C2 C3,1uF,_0402NO,2, ,
2,,CAP_CERAMIC_0805MP,C1 C8,10uF,_0805MP,2, ,
3,,STEMMA_I2C_QTSKINNY,CONN1,STEMMA_I2C_QTSKINNY,JST_SH4_SKINNY,1, ,
4,,DIODE_SOD323MINI,D1,NSR0320,SOD-323_MINI,1, ,
5,,ATSAMD21E,IC3,ATSAMD21E,QFN32_5MM,1, ,
6,,HEADER-1X7_CASTEL,JP1 JP3,HEADER-1X7_CASTEL,1X07_CASTEL,2, ,
7,,WS2812B_SK6805_1515,LED1,WS2812B_SK6805_1515,SK6805_1515,1, ,
8,,SWITCH_TACT_SMT4.6X2.8,Q2,reset,BTN_KMR2_4.6X2.8,1, ,
9,,RESISTOR_0402NO,R1 R5 R6,5.1K,_0402NO,3, ,
10,,"TPB1,27",SWC0 SWC1 SWD0,"TPB1,27","B1,27",3, ,
11,,VREG_SOT23-5,U1,AP2112K-3.3,SOT23-5,1, ,
12,,SPIFLASH_8PIN,U2,SPIFLASH_8PIN,SOIC8_150MIL,1, ,
13,,USB_C,X6,USB TYPE C,USB_C_CUSB31-CFM2AX-01-X,1, ,





Project info:
Schematic:,working
Variant:,default
Revision:,
Date:,2023-08-03_17-21-23
KiCad Version:,7.0.6-7.0.6~ubuntu22.04.1
Statistics:
Component Groups:,13
Component Count:,20 (0 SMD/ 0 THT)
Fitted Components:,20 (0 SMD/ 0 THT)
Number of PCBs:,1
Total Components:,20
